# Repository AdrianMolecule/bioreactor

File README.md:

# bioreactor
Hi there! Welcome to the Bioreactor repository. While a lot of information is still stored in other repositories like Slack, Google Docs and different clouds this is pretty comprehensive and usable.

Please be aware this is work in progress and sometimes the most recent version is under the cloud storage for the specific application.

For software please look under src firmware for most of the code. You will need to use Eclipse and we have a config guide under docs.
The Blocky interpreter will be added soon and initially will be using Visual Studio but that might change.

For electronics you can find descriptive pdf files for all the boards and the corresponding schematics and PCB layouts under electronics. They don't change a lot, so most likely what you see in here is the latest stable board.

For mechanics you can find the Fusion 360 files for the main body under mechanics. Some of the smaller parts that are 3d printed are designed using Tinkercad. Newer ones are done in Fusion 360 or OpenCad as we move away from Tinkercad.

Most of the images and some videos are under docs images. Sometimes an image is worth 1000 words.

There is a boilerplate paper which highlights the generic editing yet it is is just a place to gather paper materials.

We also have a spreadsheet with the parts yet that is a little bit of a moving target as we enhance the design and experiment with newer parts.

Several folders like management-interface, server and controller contain experimental material

Below you can find a brief info about setting up the device, for other questions feel to shoot [us](https://github.com/liquidatom) a message.

## Quick Start

1. Assemble the device 
2. [Configure eclipse](https://github.com/AdrianMolecule/bioreactor/blob/master/docs/Configuring%20Eclipse%20to%20run%20ESP32.md)  
3. Build and upload firmware
4. Configure bioreactor using [this](https://github.com/AdrianMolecule/bioreactor/tree/master/docs/manual%20bioreactor%20v1.pdf) manual
5. use the ODmeter readme to install the ODMeter

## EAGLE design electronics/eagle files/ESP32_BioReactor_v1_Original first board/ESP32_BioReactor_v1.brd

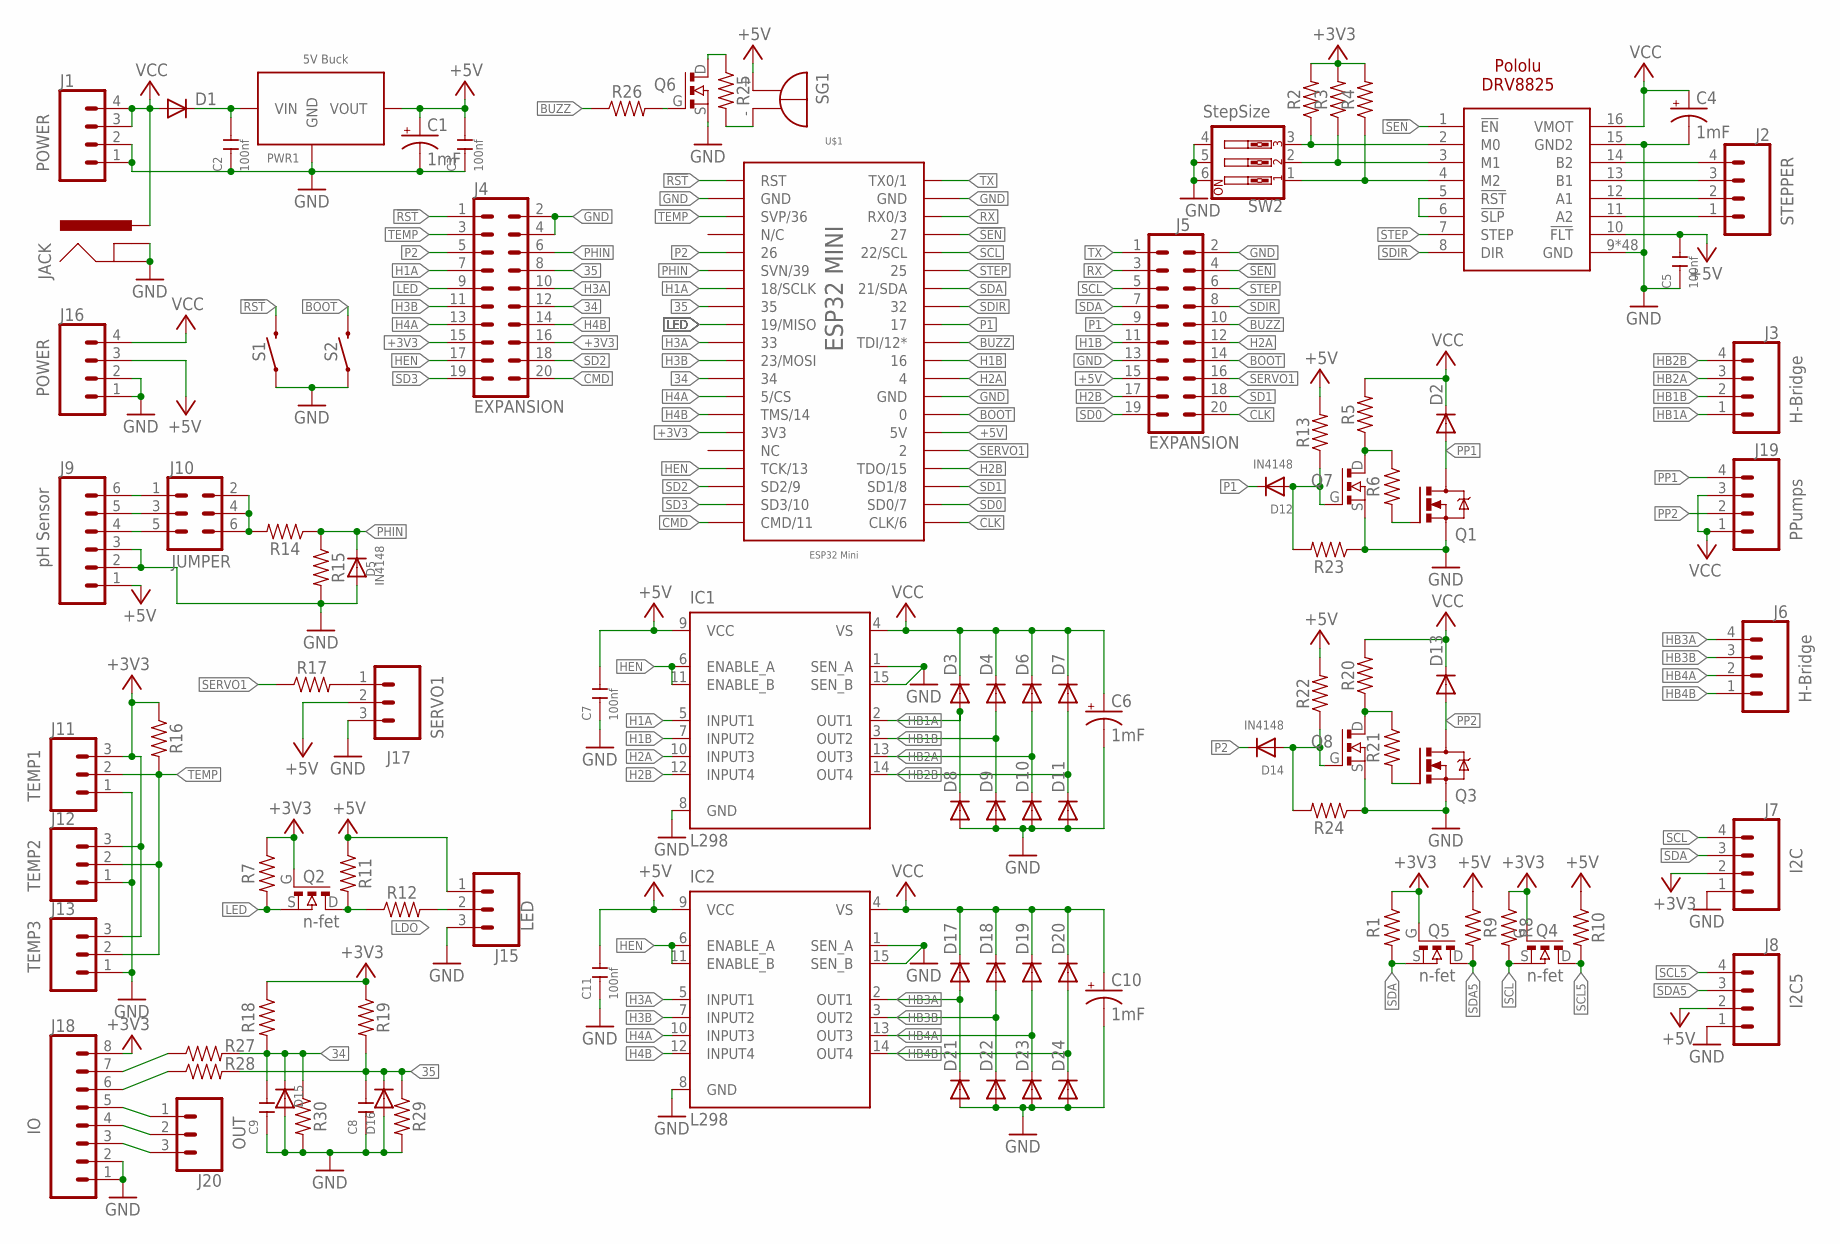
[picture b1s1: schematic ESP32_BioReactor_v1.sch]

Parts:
C1, C4, C6, C10: 1mF; CPOL-RADIAL-5MM-10MM
C2, C3, C5, C7, C8, C9, C11: 100nf; CERAMIC-2.54
D1, D2, D3, D4, D6, D7, D8, D9, D10, D11, D13, D17, D18, D19, D20, D21, D22, D23, D24: 1N4004; DO41-10
D5, D12, D14, D15, D16: IN4148; DO-1N4148
DR1: DRV8825; POLOLU-DRV8825
IC1, IC2: L298; MULTIWATT-15
J1, J16: POWER; 1X04_LONGPADS
J2: STEPPER; 1X04_LONGPADS
J3, J6: H-Bridge; 1X04_LONGPADS
J4, J5: EXPANSION; 2X10_NOSILK
J7: I2C; 1X04_LONGPADS
J8: I2C5; 1X04_LONGPADS
J9: pH Sensor; 1X06_LONGPADS
J10: JUMPER; 2X3
J11: TEMP1; 1X03_LONGPADS
J12: TEMP2; 1X03_LONGPADS
J13: TEMP3; 1X03_LONGPADS
J15: LED; 1X03_LONGPADS
J17: SERVO1; 1X03_LONGPADS
J18: IO; 1X08_LONGPADS
J19: PPumps; 1X04_LONGPADS
J20: OUT; 1X03
JACK: POWER_JACKPTH_LOCK; POWER_JACK_PTH_LOCK
PWR1: 5V Buck; 5VBUCK
Q1, Q3: IRF740; TO220BV
Q2, Q4, Q5: n-fet; TO92260P520H533-3
Q6, Q7, Q8: 2N7000; TO92260P520H533-3
R1, R2, R3, R4, R5, R6, R7, R8, R9, R10, R11, R12, R13, R14, R15, R16, R17, R18, R19, R20, R21, R22, R23, R24, R25, R26, R27, R28, R29, R30: 10k; AXIAL-0.3
S1, S2: MOMENTARY-SWITCH-SPST-PTH-6.0MM; TACTILE_SWITCH_PTH_6.0MM
SG1: F/HMB
SW2: StepSize; EDG-03
U$1: ESP32 Mini; ESP32MINI

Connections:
34: C9.2, D15.C, J4.12, R18.P$2 (2), R27.P$2 (2), R30.P$1 (1), U$1.34
35: C8.2, D16.C, J4.8, R19.P$2 (2), R28.P$2 (2), R29.P$1 (1), U$1.35
!RST: J4.1, S1.3 (2), U$1.RST
!SEN: DR1.1 (!EN), J5.4, U$1.27
+3V3: J4.15, J4.16, J7.2, J11.3, J12.3, J13.3, J18.8, Q2.G, Q4.G, Q5.G, R1.P$1 (1), R2.P$2 (2), R3.P$2 (2), R4.P$2 (2), R7.P$1 (1), R8.P$1 (1), R16.P$1 (1), R18.P$1 (1), R19.P$1 (1), U$1.3V3
+5V: C1.+, C3.2, C5.2, C7.2, C11.2, DR1.10 (!FLT), IC1.9 (VCC), IC2.9 (VCC), J5.15, J8.2, J9.1, J15.1, J16.3, J17.2, PWR1.VOUT, R9.P$1 (1), R10.P$1 (1), R11.P$1 (1), R13.P$2 (2), R22.P$2 (2), SG1.+, U$1.5V
BOOT: J5.14, S2.3 (2), U$1.0
BUZZ: J5.10, R26.P$1 (1), U$1.TDI (TDI/12*)
CLK: J5.20, U$1.CLK (CLK/6)
CMD: J4.20, U$1.CMD (CMD/11)
GND: C1.-, C2.1, C3.1, C4.-, C5.1, C6.-, C7.1, C8.1, C9.1, C10.-, C11.1, D5.A, D8.A, D9.A, D10.A, D11.A, D15.A, D16.A, D21.A, D22.A, D23.A, D24.A, DR1.9 (GND), DR1.15 (GND2), DR1.GND@1 (GND), DR1.GND@2 (GND), DR1.GND@3 (GND), DR1.GND@4 (GND), DR1.GND@5 (GND), DR1.GND@6 (GND), DR1.GND@7 (GND), DR1.GND@8 (GND), DR1.GND@9 (GND), DR1.GND@10 (GND), DR1.GND@11 (GND), DR1.GND@12 (GND), DR1.GND@13 (GND), DR1.GND@14 (GND), DR1.GND@15 (GND), DR1.GND@16 (GND), DR1.GND@17 (GND), DR1.GND@18 (GND), DR1.GND@19 (GND), DR1.GND@20 (GND), DR1.GND@21 (GND), DR1.GND@22 (GND), DR1.GND@23 (GND), DR1.GND@24 (GND), DR1.GND@25 (GND), DR1.GND@26 (GND), DR1.GND@27 (GND), DR1.GND@28 (GND), DR1.GND@29 (GND), DR1.GND@30 (GND), DR1.GND@31 (GND), DR1.GND@32 (GND), DR1.GND@33 (GND), DR1.GND@34 (GND), DR1.GND@35 (GND), DR1.GND@36 (GND), DR1.GND@37 (GND), DR1.GND@38 (GND), DR1.GND@39 (GND), DR1.GND@40 (GND), DR1.GND@41 (GND), DR1.GND@42 (GND), DR1.GND@43 (GND), DR1.GND@44 (GND), DR1.GND@45 (GND), DR1.GND@50 (GND), DR1.GND@51 (GND), IC1.1 (SEN_A), IC1.8 (GND), IC1.15 (SEN_B), IC2.1 (SEN_A), IC2.8 (GND), IC2.15 (SEN_B), J1.1, J1.2, J4.2, J4.4, J5.2, J5.13, J7.1, J8.1, J9.2, J9.3, J11.1, J12.1, J13.1, J15.3, J16.1, J16.2, J17.3, J18.1, J18.2, JACK.GND, JACK.GNDBREAK, PWR1.GND, Q1.S, Q3.S, Q6.S, Q7.S, Q8.S, R15.P$2 (2), R23.P$1 (1), R24.P$1 (1), R29.P$2 (2), R30.P$2 (2), S1.1, S2.1, SW2.4, SW2.5, SW2.6, U$1.GND@1 (GND), U$1.GND@2 (GND), U$1.GND@3 (GND)
H1A: IC1.5 (INPUT1), J4.7, U$1.18 (18/SCLK)
H1B: IC1.7 (INPUT2), J5.11, U$1.16
H2A: IC1.10 (INPUT3), J5.12, U$1.4
H2B: IC1.12 (INPUT4), J5.17, U$1.TDO (TDO/15)
H3A: IC2.5 (INPUT1), J4.10, U$1.33
H3B: IC2.7 (INPUT2), J4.11, U$1.23 (23/MOSI)
H4A: IC2.10 (INPUT3), J4.13, U$1.5 (5/CS)
H4B: IC2.12 (INPUT4), J4.14, U$1.TMS (TMS/14)
HB1A: D3.A, D8.C, IC1.2 (OUT1), J3.1
HB1B: D4.A, D9.C, IC1.3 (OUT2), J3.2
HB2A: D6.A, D10.C, IC1.13 (OUT3), J3.3
HB2B: D7.A, D11.C, IC1.14 (OUT4), J3.4
HB3A: D17.A, D21.C, IC2.2 (OUT1), J6.4
HB3B: D18.A, D22.C, IC2.3 (OUT2), J6.3
HB4A: D19.A, D23.C, IC2.13 (OUT3), J6.2
HB4B: D20.A, D24.C, IC2.14 (OUT4), J6.1
HEN: IC1.6 (ENABLE_A), IC1.11 (ENABLE_B), IC2.6 (ENABLE_A), IC2.11 (ENABLE_B), J4.17, U$1.TCK (TCK/13)
LDO: J15.2, R12.P$2 (2)
LED: J4.9, Q2.S, R7.P$2 (2), U$1.19 (19/MISO)
unnamed: DR1.3 (M1), R3.P$1 (1), SW2.2
unnamed: C2.2, D1.C, PWR1.VIN
unnamed: DR1.4 (M2), R4.P$1 (1), SW2.1
unnamed: Q7.D, R5.P$1 (1), R6.P$1 (1)
unnamed: DR1.5 (!RST), DR1.6 (!SLP)
unnamed: J10.2, J10.4, J10.6, R14.P$2 (2)
unnamed: Q1.G, R6.P$2 (2)
unnamed: DR1.2 (M0), R2.P$1 (1), SW2.3
unnamed: Q8.D, R20.P$1 (1), R21.P$1 (1)
unnamed: R25.P$2 (2), SG1.-
unnamed: Q3.G, R21.P$2 (2)
unnamed: DR1.11 (A2), J2.1
unnamed: DR1.12 (A1), J2.2
unnamed: DR1.13 (B1), J2.3
unnamed: DR1.14 (B2), J2.4
unnamed: D14.A, Q8.G, R22.P$1 (1), R24.P$2 (2)
unnamed: J9.4, J10.5
unnamed: Q6.D, R25.P$1 (1)
unnamed: Q6.G, R26.P$2 (2)
unnamed: J9.5, J10.3
unnamed: J9.6, J10.1
unnamed: D12.A, Q7.G, R13.P$1 (1), R23.P$2 (2)
unnamed: Q2.D, R11.P$2 (2), R12.P$1 (1)
unnamed: J17.1, R17.P$2 (2)
unnamed: J18.5, J20.1
unnamed: J18.4, J20.2
unnamed: J18.3, J20.3
unnamed: J18.6, R28.P$1 (1)
unnamed: J18.7, R27.P$1 (1)
P1: D12.C, J5.9, U$1.17
P2: D14.C, J4.5, U$1.26
PHIN: D5.C, J4.6, R14.P$1 (1), R15.P$1 (1), U$1.SVN (SVN/39)
PP1: D2.A, J19.4, Q1.D
PP2: D13.A, J19.2, Q3.D
RX: J5.3, U$1.RX0 (RX0/3)
SCL: J5.5, J7.4, Q4.S, R8.P$2 (2), U$1.22 (22/SCL)
SCL5: J8.4, Q4.D, R10.P$2 (2)
SD0: J5.19, U$1.SD0 (SD0/7)
SD1: J5.18, U$1.SD1 (SD1/8)
SD2: J4.18, U$1.SD2 (SD2/9)
SD3: J4.19, U$1.SD3 (SD3/10)
SDA: J5.7, J7.3, Q5.S, R1.P$2 (2), U$1.21 (21/SDA)
SDA5: J8.3, Q5.D, R9.P$2 (2)
SDIR: DR1.8 (DIR), J5.8, U$1.32
SERVO1: J5.16, R17.P$1 (1), U$1.2
STEP: DR1.7 (STEP), J5.6, U$1.25
TEMP: J4.3, J11.2, J12.2, J13.2, R16.P$2 (2), U$1.SVP (SVP/36)
TX: J5.1, U$1.TX0 (TX0/1)
VCC: C4.+, C6.+, C10.+, D1.A, D2.C, D3.C, D4.C, D6.C, D7.C, D13.C, D17.C, D18.C, D19.C, D20.C, DR1.16 (VMOT), IC1.4 (VS), IC2.4 (VS), J1.3, J1.4, J16.4, J19.1, J19.3, JACK.PWR, R5.P$2 (2), R20.P$2 (2)

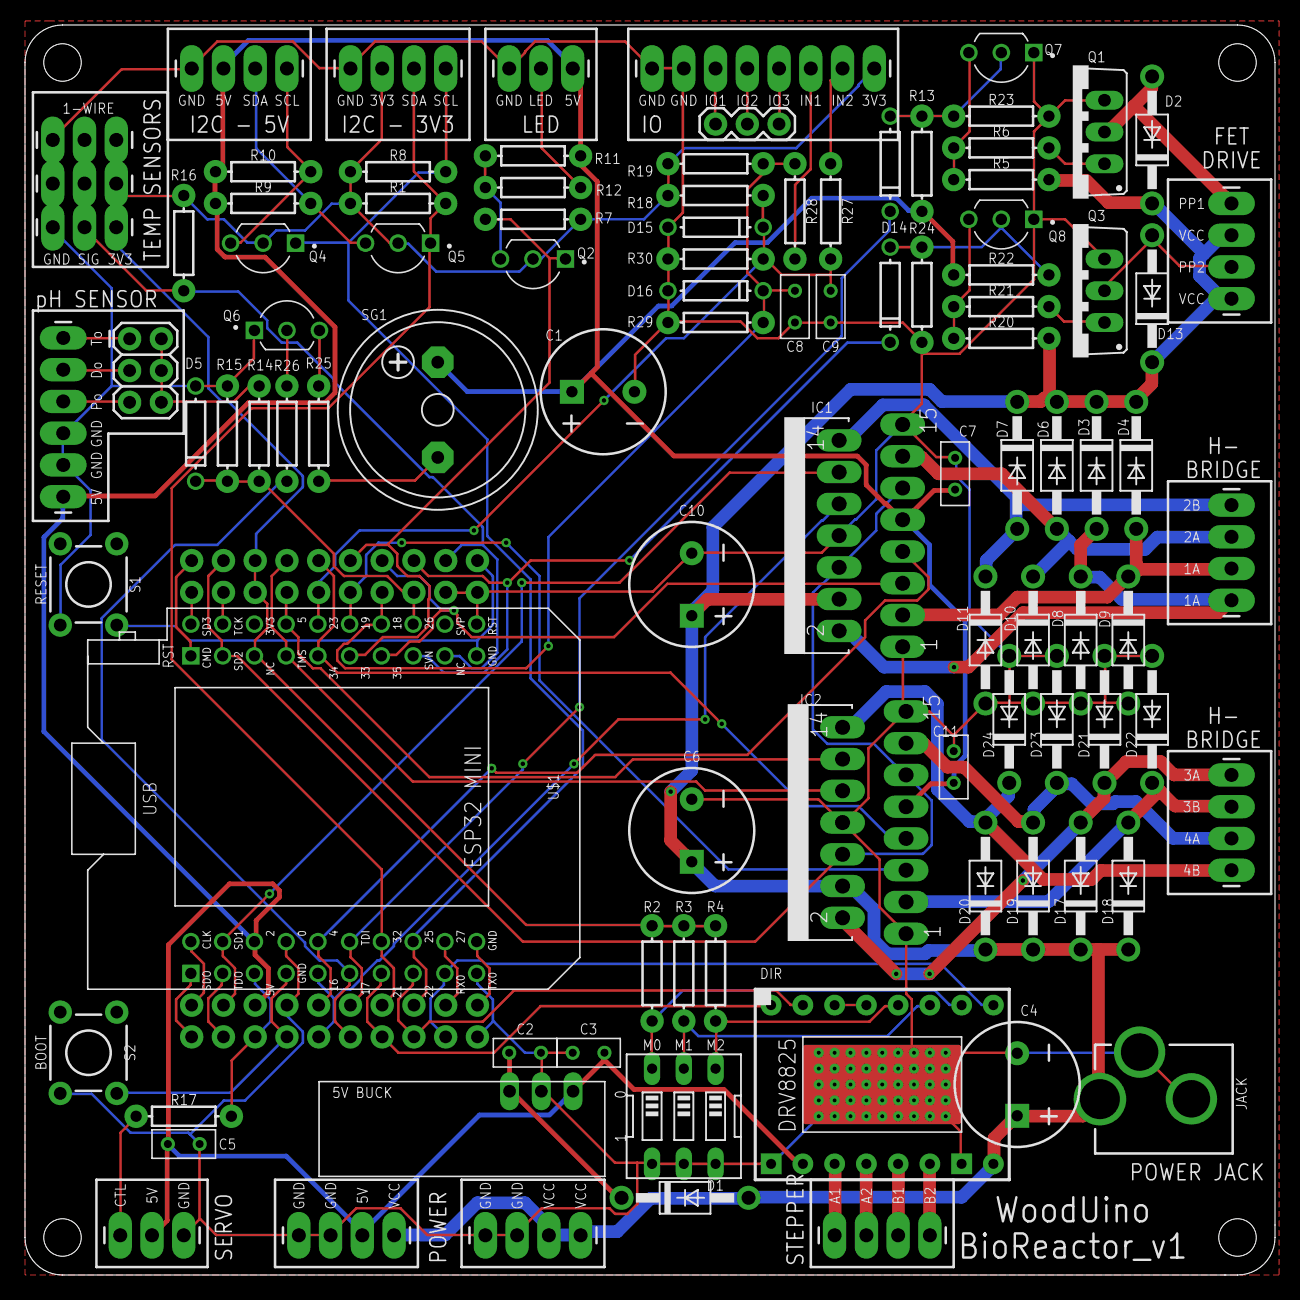
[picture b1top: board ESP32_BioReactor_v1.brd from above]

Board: 2 copper layers, 100.0 x 100.0 mm, 102 parts (0 on the bottom side), 79 nets.

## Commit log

2020-04-02 Create mechanical
2020-04-06 eclipse doc
2020-04-06 Update ESP_with_eclipse.md
    update eclipse doc
2020-04-06 add first draft of schema for bioreactor protocols
2020-04-06 fix minor errors in json examples
2020-04-09 add initial code from adrian
2020-04-09 add script to create the gcloud project
2020-04-09 gitignore node_modules
2020-04-09 add code to setup GKE cluster
2020-04-10 Rename ESP_with_eclipse.md to Configuring Eclipse to run ESP32.md
2020-04-10 wifi example
2020-04-11 create display interface
2020-04-11 Initial commit
    Creating the public server and control part of the bioreactor. Just include the scaffolded Angular application.
2020-04-11 Production
    Build the client in production mode by default
2020-04-12 Overview of the bioreactor software.
2020-04-12 consistency tweak
2020-04-12 more consistency twek
2020-04-12 wording
2020-04-22 temperature reading & websockets
2020-05-07 ph sensor
2020-05-17 save program and wifi settings in flash memory
2020-05-26 migrate to sloeber
2020-05-27 join sensor code
2020-06-04 doc for Sloeber plugin
2020-06-14 manage FET & HBridge outputs
2020-06-14 faster upload speed & dependencies
2020-06-14 UI Intial Commit
2020-06-14 fixed temp sensor
2020-06-14 modifying reactor state from web
2020-06-14 fixing html
2020-06-15 cleaned up firmware related files and folders
2020-06-23 OTA program upload
2020-07-05 response after program and file upload
2020-07-05 Custom Blockly blocks
2020-09-02 Bump bl from 4.0.2 to 4.0.3 in /controller
    Bumps [bl](https://github.com/rvagg/bl) from 4.0.2 to 4.0.3.
    - [Release notes](https://github.com/rvagg/bl/releases)
    - [Commits](https://github.com/rvagg/bl/compare/v4.0.2...v4.0.3)
2020-10-12 static file serve
2020-11-15 basic of reactor launch
2020-11-21 reactor status in footer
2020-11-21 refactoring reactor->actuators interaction
2020-12-06 fixed memory overrun
2020-12-12 Bump ini from 1.3.5 to 1.3.8 in /controller
    Bumps [ini](https://github.com/isaacs/ini) from 1.3.5 to 1.3.8.
    - [Release notes](https://github.com/isaacs/ini/releases)
    - [Commits](https://github.com/isaacs/ini/compare/v1.3.5...v1.3.8)
2020-12-14 move motor code to actuators
2021-01-08 read only one temp sensor
2021-01-30 calibrating ph
2021-02-25 running stepper in separate thread
2021-02-25 run motor without running the program
2021-02-25 disabling buzzer
2021-03-13 sensor update rate and readings collectioin
2021-05-08 pwm and manual
2021-05-12 PWM & slider for FETs
2021-05-14 pwm and sliders for bridge
2021-05-14 remove off state for bridges
2021-06-24 working pwm
2021-10-29 add desired zone on graphs
2021-11-08 store sensor readings
2021-11-16 view last batch data
2021-11-18 minor UI changes
2021-11-19 adding docs
2021-12-12 dump cache data in file
2021-12-12 update project settings
2021-12-18 fix bug with enabling motor
2022-02-11 Bump karma from 4.4.1 to 6.3.14 in /server/public/bioreactor-monitor
    Bumps [karma](https://github.com/karma-runner/karma) from 4.4.1 to 6.3.14.
    - [Release notes](https://github.com/karma-runner/karma/releases)
    - [Changelog](https://github.com/karma-runner/karma/blob/master/CHANGELOG.md)
    - [Commits](https://github.com/karma-runner/karma/compare/v4.4.1...v6.3.14)
    ---
    updated-dependencies:
2022-02-11 changed sensor reading cache
2022-02-11 config update
2022-03-02 Bump karma from 4.4.1 to 6.3.16 in /server/public/bioreactor-monitor
    Bumps [karma](https://github.com/karma-runner/karma) from 4.4.1 to 6.3.16.
    - [Release notes](https://github.com/karma-runner/karma/releases)
    - [Changelog](https://github.com/karma-runner/karma/blob/master/CHANGELOG.md)
    - [Commits](https://github.com/karma-runner/karma/compare/v4.4.1...v6.3.16)
    ---
    updated-dependencies:
2022-03-16 Main bioreactor board version 1.1 and potentistat board 1.0
    The main board in Eagle format including documentation pdfs
    also the full breakout board for reading the dissolved Oxigen via a potentiostat device
2022-03-16 this was supposed to be a folder
    file delete
2022-03-16 moved external documentation in GitHub
    moved external documentation in GitHub
2022-03-16 more images
2022-03-16 moved documents from other storage
2022-03-16 moved documents from Google Drive and other sources
2022-03-16 moved to gitHub
2022-03-16 Orbital shaker box and box generator script
2022-03-17 support motor rpm
2022-03-17 enable http cache for static files
2022-03-18 Added interpreter for blockly integration
2022-03-21 Enzyme cooler
    Enzyme cooler
2022-03-22 refactor
2022-03-22 added BOM
2022-03-22 added some screenshots
    added some screenshots
2022-03-22 clarifications
    clarifications
2022-03-23 separated wet components
    separated wet components
2022-03-23 wet parts changes
    wet parts changes
2022-03-23 Create enz one two parts 2 v3.f3d
    holder + tube +mold for washer
2022-03-25 updates
    updates
2022-03-26 Bump minimist from 1.2.5 to 1.2.6 in /controller
    Bumps [minimist](https://github.com/substack/minimist) from 1.2.5 to 1.2.6.
    - [Release notes](https://github.com/substack/minimist/releases)
    - [Commits](https://github.com/substack/minimist/compare/1.2.5...1.2.6)
    ---
    updated-dependencies:
    - dependency-name: minimist
2022-04-02 update
    update
2022-04-03 old obsolete stuff
2022-04-03 Bump url-parse from 1.4.7 to 1.5.10 in /server/public/bioreactor-monitor
    Bumps [url-parse](https://github.com/unshiftio/url-parse) from 1.4.7 to 1.5.10.
    - [Release notes](https://github.com/unshiftio/url-parse/releases)
    - [Commits](https://github.com/unshiftio/url-parse/compare/1.4.7...1.5.10)
    ---
    updated-dependencies:
    - dependency-name: url-parse
2022-04-03 Bump lodash from 4.17.15 to 4.17.21 in /server/public/bioreactor-monitor
    Bumps [lodash](https://github.com/lodash/lodash) from 4.17.15 to 4.17.21.
    - [Release notes](https://github.com/lodash/lodash/releases)
    - [Commits](https://github.com/lodash/lodash/compare/4.17.15...4.17.21)
    ---
    updated-dependencies:
    - dependency-name: lodash
2022-04-03 old obsolete
2022-04-07 Create AdrianOriginalMach3mill.cps
    modified to show XYZ min and max
2022-04-07 reactor
2022-04-14 results in running the OS for > 8 hours at 300 RPM with 50ml LB media in 100ml flask
    results in running the OS for > 8 hours at 300 RPM with 50ml LB media in 100ml flask
2022-04-19 some fuGFP and OpticalDensity data
2022-04-21 more stuff for the OS
2022-04-22 winged nuts
2022-04-24 more pics
2022-04-26 code works
2022-04-29 more updates
2022-06-09 Backup of FUsion360 on June 8th
    Backup of FUsion360 on June 8th
2022-06-10 shipped bioreactor to Danny Chan
2022-06-16 new box and smaller axis and big case for standalone Optical density meter
2022-06-22 mostly documentation
    mostly documentation
2022-06-24 o lot of images
2022-06-27 many running bioreactors
2022-06-27 biorectors movie
2022-06-29 images updates
2022-06-29 organized incubator
2022-06-29 personal incubator with window
2022-07-19 added code pre Cambridge workshop
    added code pre Cambridge workshop
2022-07-19 better file names

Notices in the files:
parts and their libraries:
SparkFun-Connectors: Licensing: Creative Commons ShareAlike 4.0 International - https://creativecommons.org/licenses/by-sa/4.0
